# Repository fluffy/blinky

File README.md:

# blinky

Blinking lights to tell time. And it beeps.

# Build and flash

Build with:
```
mkdir build ; cd build ; cmake .. ; make
```

Note when programming the GPS board, the GPS must be unplugged while
programming.

Program flash using stlink with:
```
st-flash --reset --format ihex write build/blinky.hex
```

Can program using Stm32CubeProgrammer with RTS=1, DTR=0, baud at 115200,
Parity Even, data bits 8, stop bits 1, flow control off.

Program flash using USB serial with:
```
stm32flash -w build/blinky.hex -v -b 115200 -m 8e1 -i "-dtr," /dev/cu.usbserial-31110
```

If this fails, try the following reset then try to flash again. This
will not work on a brand new uninitialized board, the board needs to be
programmed for the first time with st-flash.

Can reset the board with:
```
stty -f /dev/cu.usbserial-31110 hup
```

Monitor output connect with Serial program. Use 115200 baud with 8 bits,
no parity, 1 stop bit. Set the RTS and DTR both low. Screen fails to do
this. It sets RTS and DTR both high it will not work.

To use python miniterm (replace usbserial-31110 with number on your machine):
```
pyserial-miniterm -e --parity N --rts 0 --dtr 0 /dev/cu.usbserial-31110 115200
```
Can exit the miniterm with CTRL+]. This will cause board reset when it starts.

# Tools and Dependencies

Set up a mac to be able to build by installing:

* TODO
* pip3 install pyserial

# Features

## Blink Timing Board

On the Rev A hardware 1.0 software have:

* Timing board with TXCO, LTC Sync in, LTC Sync out, LED grid,
  battery power, USB debug, audio in/out

* Display 120 fps tick on 10x4 grid
* 3.3V LTC Sync Out
* PPS out is hold sync button while booting
* Jitter of less than 1 ms
* Jam sync to 3.3V Sync input
* Time drift of < 5 ms in 1 hour
* USB port for serial data
* read  calibration from EEPROM
* audio out of beep
* headset monitor of audio out
* usb upgrade of firmware
* Status LEDs: error(red), external synced (green),  not sync (
  blue ), have sync (teal)
* audio input to detect beep
* battery with 2h life and USB charger

## Clock and GPS Board

On the Rev A hardware 0.2 software have:

* GPS board with GPS, OCXO
* LTC sync out, LTC sync in
* Does not have audio or led display grid
* 10 MHz sine wave output 1V p2p into 50 ohm, 3 channels
* Sync to GPS PPS
* Show current PPS offset from GPS PPS
* Compare PPS accuracy to GPS over 24 hours
* read  calibration from EEPROM
* USB serial display of: Time, GPS Error, SyncIn Error
* Aux input of 10 MHz signal to compare
* PPS jitter of about +/- 20 ns and error less than 10 ns
* USB upgrade of firmware
* USB 3A power for gps board
* USB output serial data for computer time sync

## Light GPS Board

On the Rev A hardware 0.2 software have:

* GPS board with GPS
* LTC sync out
* Does not have audio or led display grid
* Sync to GPS PPS
* USB upgrade of firmware
* USB power
* USB output serial data for computer time sync

## Wishlist

* time into browser measure computer time offset
* software upgrade from browser

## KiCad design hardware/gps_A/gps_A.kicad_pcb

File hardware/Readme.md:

# Notes on updating hardware

If the schematic or boards in changed such that the software can tell
the difference, the rev need to go up a letter. Other changes can get a
sub number on the rev letter.

## Schematics

Don't update sybols  / footprint from libraries. It over writes stuff.

When done, do a plot to generate schematic in production subdir.

## PCB

When done, do an export of step to generate a model in production
subdir.

## JLCPCB

Make sure to have them check part placement becuase it will be
wrong. Even what they have in the preivewi tool does not allways match
what they have in productions.

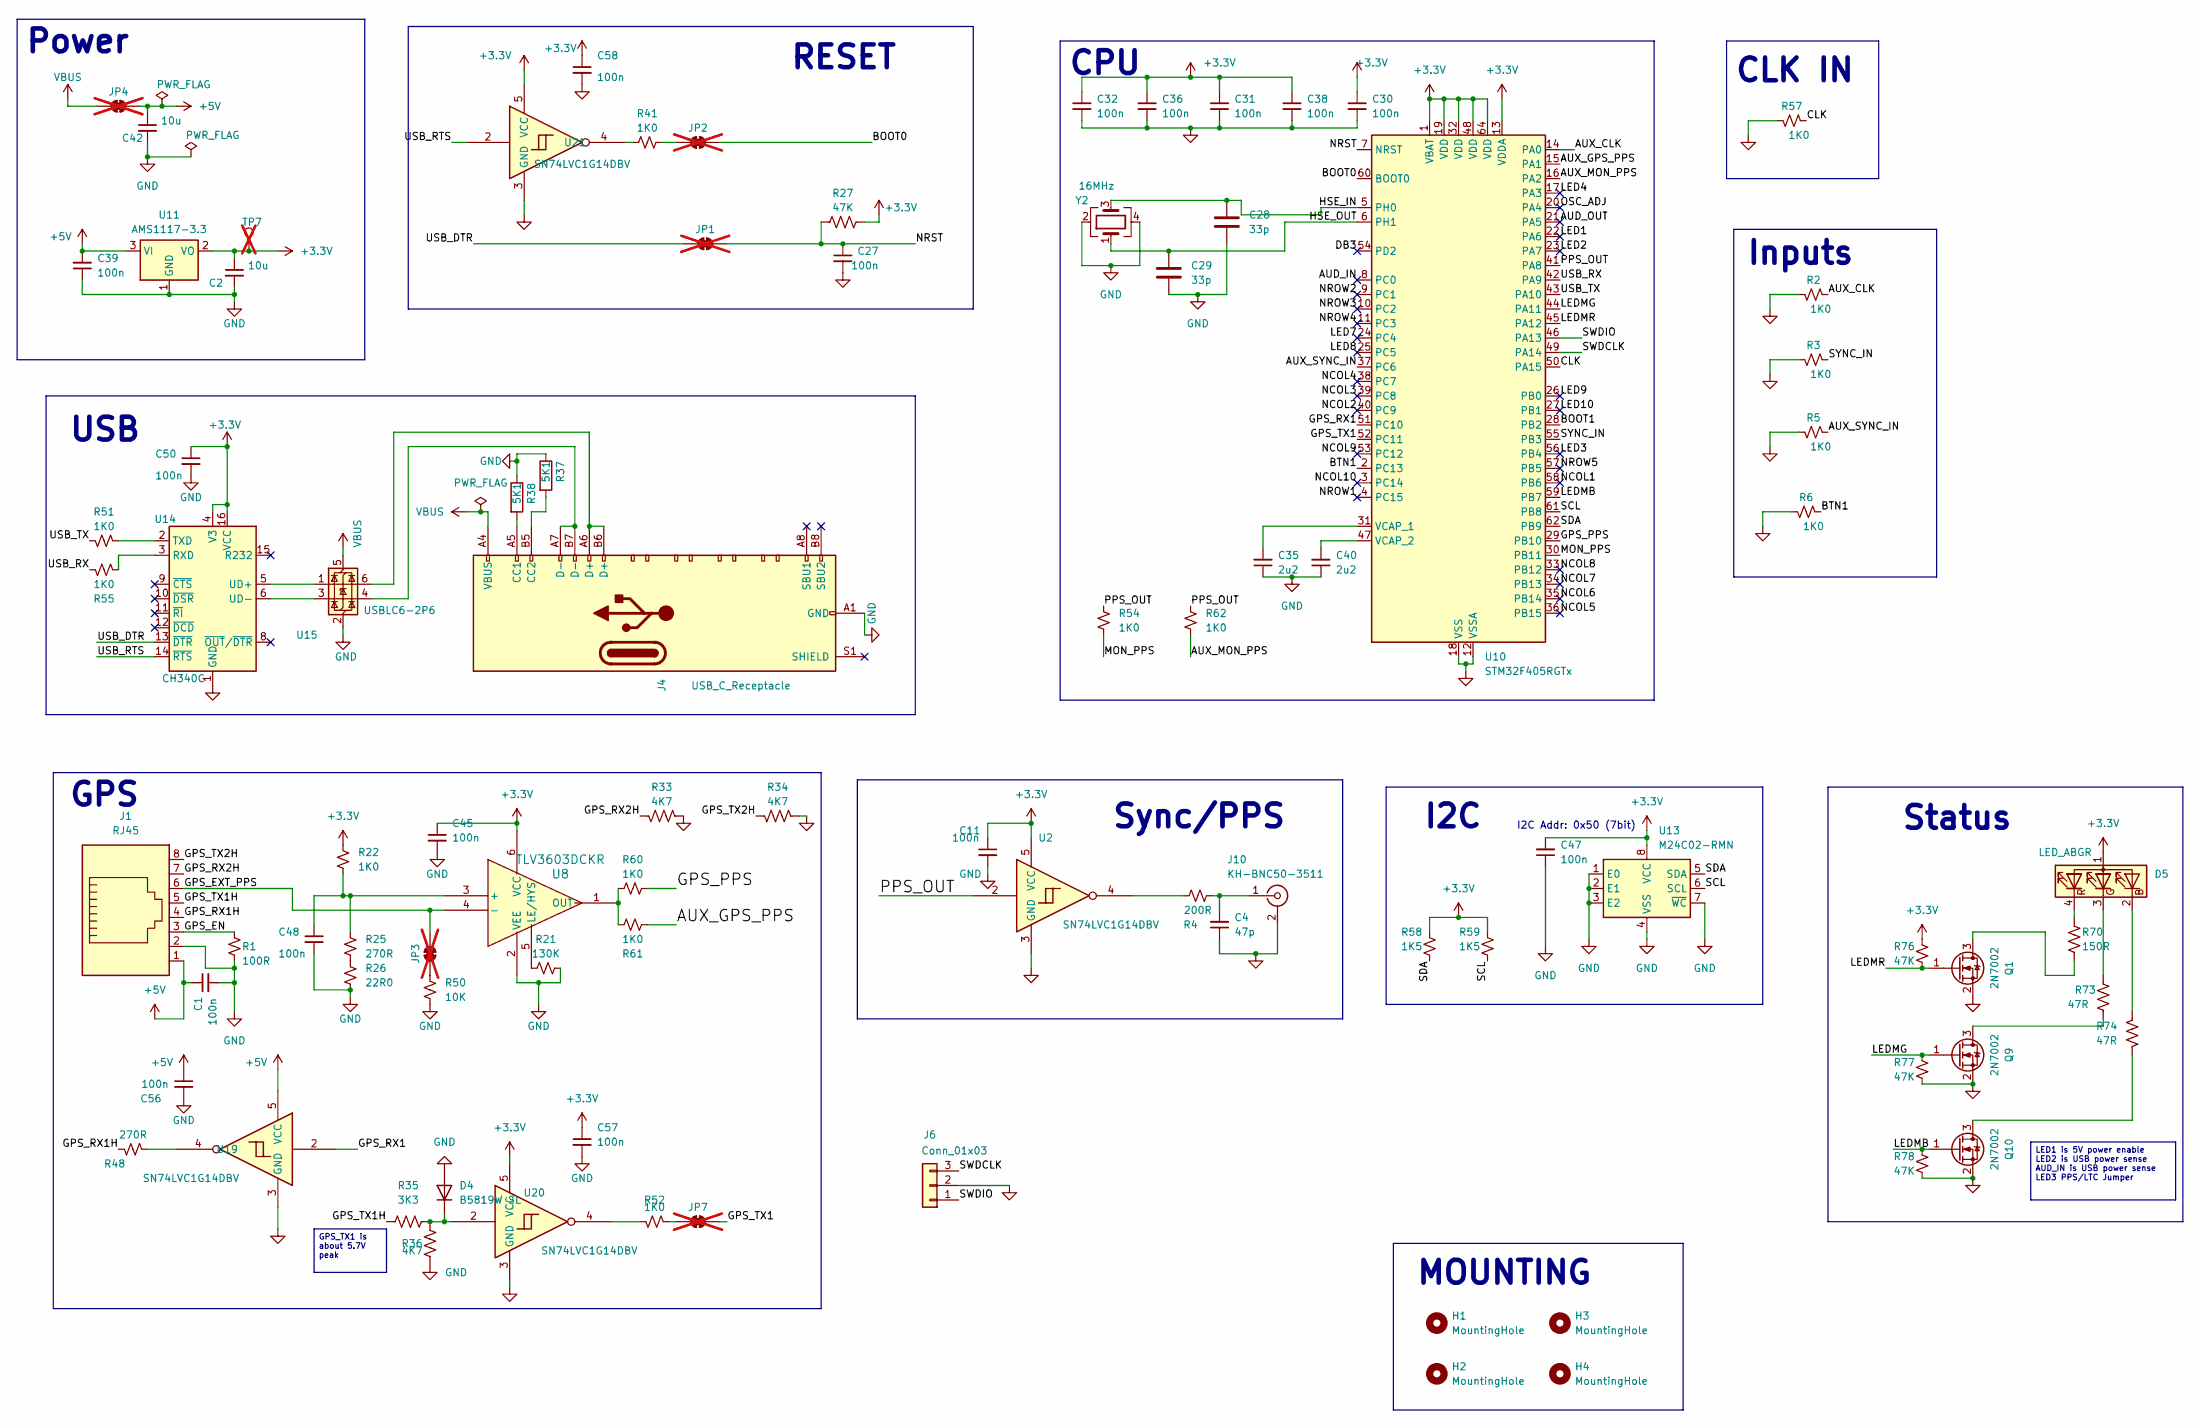
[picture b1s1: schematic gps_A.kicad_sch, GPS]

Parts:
C1, C11, C30, C31, C32, C36, C38, C39, C45, C47, C48, C50, C56, C57, C58: 100n; C_0402_1005Metric; JLCPCB Part # C307331
C2, C42: 10u; C_0603_1608Metric; JLCPCB Part # C19702
C4: 47p; C_0603_1608Metric; JLCPCB Part # C1671
C27: 100n; C_0603_1608Metric; JLCPCB Part # C14663
C28, C29: 33p; C_0603_1608Metric; JLCPCB Part # C1663
C35, C40: 2u2; C_0603_1608Metric; JLCPCB Part # C23630
D4: B5819W SL; D_SOD-123; JLCPCB Part # C8598
D5: LED_ABGR; LED_RGB_MHS110FRGBCT; MPN MHS110FRGBCT; JLCPCB Part # C496820
H1, H2, H3, H4: MountingHole; MountingHole_2.2mm_M2
J1: RJ45; RJ45_Amphenol_RJHSE5380; JLCPCB Part # C464586
J4: USB_C_Receptacle; USB_C_Receptacle_HRO_TYPE-C-31-M-12; JLCPCB Part # C165948
J6: Conn_01x03; JST_PH_S3B-PH-SM4-TB_1x03-1MP_P2.00mm_Horizontal; JLCPCB Part # C265101
J10: KH-BNC50-3511; BNC_Amphenol_B6252HB-NPP3G-50_Horizontal-CJ; JLCPCB Part # C2837587
JP1, JP2, JP3, JP4, JP7: SolderJumper_2_Bridged; SolderJumper-2_P1.3mm_Bridged2Bar_RoundedPad1.0x1.5mm; not fitted
Q1, Q9, Q10: 2N7002; SOT-23; JLCPCB Part # C8545
R1: 100R; R_0603_1608Metric; JLCPCB Part # C22775
R2, R3, R5, R6, R22, R41, R51, R52, R54, R55, R57, R60, R61, R62: 1K0; R_0603_1608Metric; JLCPCB Part # C21190
R4: 200R; R_0603_1608Metric; JLCPCB Part # C8218
R21: 130K; R_0603_1608Metric; JLCPCB Part # C22795
R25, R48: 270R; R_0603_1608Metric; JLCPCB Part # C22966
R26: 22R0; R_0603_1608Metric; JLCPCB Part # C23345
R27, R76, R77, R78: 47K; R_0603_1608Metric; JLCPCB Part # C25819
R33, R34, R36: 4K7; R_0603_1608Metric; JLCPCB Part # C23162
R35: 3K3; R_0603_1608Metric; JLCPCB Part # C22978
R37, R38: 5K1; R_0603_1608Metric; JLCPCB Part # C23186
R50: 10K; R_0603_1608Metric; JLCPCB Part # C25804
R58, R59: 1K5; R_0603_1608Metric; JLCPCB Part # C22843
R70: 150R; R_0603_1608Metric; JLCPCB Part # C22808
R73, R74: 47R; R_0603_1608Metric; JLCPCB Part # C23182
TP7: TestPoint_THTPad_D1.5mm_Drill0.7mm; not fitted
U2, U19, U20, U21: SN74LVC1G14DBV; SOT-23-5; JLCPCB Part # C133145
U8: TLV3603DCKR; SOT-363_SC-70-6; JLCPCB Part # C5213955
U10: STM32F405RGTx; LQFP-64_10x10mm_P0.5mm; JLCPCB Part # C15742
U11: AMS1117-3.3; SOT-223-3_TabPin2; JLCPCB Part # C6186
U13: M24C02-RMN; SOIC-8_3.9x4.9mm_P1.27mm; JLCPCB Part # C83836
U14: CH340C; SOIC-16_3.9x9.9mm_P1.27mm; JLCPCB Part # C7464026
U15: USBLC6-2P6; SOT-666; JLCPCB Part # C2827693
Y2: 16MHz; Crystal_SMD_3225-4Pin_3.2x2.5mm; JLCPCB Part # C13738

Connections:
+3.3V: C2.1, C11.1, C30.1, C31.1, C32.1, C36.1, C38.1, C45.1, C47.2, C50.1, C57.1, C58.1, D5.1 (A), R22.1, R27.1, R58.1, R59.1, R76.1, TP7.1, U2.5 (VCC), U8.6 (VCC), U10.1 (VBAT), U10.13 (VDDA), U10.19 (VDD), U10.32 (VDD), U10.48 (VDD), U10.64 (VDD), U11.2 (VO), U13.8 (VCC), U14.4 (V3), U14.16 (VCC), U20.5 (VCC), U21.5 (VCC)
+5V: C1.1, C39.2, C42.1, C56.1, J1.1, JP4.2 (B), U11.3 (VI), U19.5 (VCC)
/AUD_IN: U10.8 (PC0)
/AUD_OUT: U10.21 (PA5)
/AUX_CLK: R2.1, U10.14 (PA0)
/AUX_GPS_PPS: R61.2, U10.15 (PA1)
/AUX_MON_PPS: R62.2, U10.16 (PA2)
/AUX_SYNC_IN: R5.1, U10.37 (PC6)
/BOOT0: JP2.2 (B), U10.60 (BOOT0)
/BOOT1: U10.28 (PB2)
/BTN1: R6.1, U10.2 (PC13)
/CLK: R57.1, U10.50 (PA15)
/DB3: U10.54 (PD2)
/GPS_EN: J1.3, R1.1
/GPS_EXT_PPS: J1.6, JP3.2 (B), U8.4 (-)
/GPS_PPS: R60.1, U10.29 (PB10)
/GPS_RX1: U10.51 (PC10), U19.2
/GPS_RX1H: J1.4, R48.2
/GPS_RX2H: J1.7, R33.2
/GPS_TX1: JP7.2 (B), U10.52 (PC11)
/GPS_TX1H: J1.5, R35.2
/GPS_TX2H: J1.8, R34.2
/HSE_IN: C28.1, U10.5 (PH0), Y2.3
/HSE_OUT: C29.1, U10.6 (PH1), Y2.1
/LED1: U10.22 (PA6)
/LED2: U10.23 (PA7)
/LED3: U10.56 (PB4)
/LED4: U10.17 (PA3)
/LED7: U10.24 (PC4)
/LED8: U10.25 (PC5)
/LED9: U10.26 (PB0)
/LED10: U10.27 (PB1)
/LEDMB: Q10.1 (G), R78.1, U10.59 (PB7)
/LEDMG: Q9.1 (G), R77.1, U10.44 (PA11)
/LEDMR: Q1.1 (G), R76.2, U10.45 (PA12)
/MON_PPS: R54.2, U10.30 (PB11)
/NCOL1: U10.58 (PB6)
/NCOL2: U10.40 (PC9)
/NCOL3: U10.39 (PC8)
/NCOL4: U10.38 (PC7)
/NCOL5: U10.36 (PB15)
/NCOL6: U10.35 (PB14)
/NCOL7: U10.34 (PB13)
/NCOL8: U10.33 (PB12)
/NCOL9: U10.53 (PC12)
/NCOL10: U10.3 (PC14)
/NROW1: U10.4 (PC15)
/NROW2: U10.9 (PC1)
/NROW3: U10.10 (PC2)
/NROW4: U10.11 (PC3)
/NROW5: U10.57 (PB5)
/NRST: C27.1, JP1.2 (B), R27.2, U10.7 (NRST)
/OSC_ADJ: U10.20 (PA4)
/PPS_OUT: R54.1, R62.1, U2.2, U10.41 (PA8)
/SCL: R59.2, U10.61 (PB8), U13.6 (SCL)
/SDA: R58.2, U10.62 (PB9), U13.5 (SDA)
/SWDCLK: J6.3, U10.49 (PA14)
/SWDIO: J6.1, U10.46 (PA13)
/SYNC_IN: R3.1, U10.55 (PB3)
/USB_DTR: JP1.1 (A), U14.13 (~DTR)
/USB_RTS: U14.14 (~RTS), U21.2
/USB_RX: R55.1, U10.42 (PA9)
/USB_TX: R51.2, U10.43 (PA10)
GND: C1.2, C2.2, C4.1, C11.2, C27.2, C28.2, C29.2, C30.2, C31.2, C32.2, C35.1, C36.2, C38.2, C39.1, C40.1, C42.2, C45.2, C47.1, C48.2, C50.2, C56.2, C57.2, C58.2, D4.2 (A), J1.2, J4.A1 (GND), J4.A12 (GND), J4.B1 (GND), J4.B12 (GND), J6.2, J10.2 (Ext), Q1.2 (S), Q9.2 (S), Q10.2 (S), R1.2, R2.2, R3.2, R5.2, R6.2, R21.2, R26.2, R33.1, R34.1, R36.1, R37.1, R38.1, R50.2, R57.2, R77.2, R78.2, U2.3 (GND), U8.2 (VEE), U10.12 (VSSA), U10.18 (VSS), U10.63 (VSS), U11.1 (GND), U13.1 (E0), U13.2 (E1), U13.3 (E2), U13.4 (VSS), U13.7 (~WC), U14.1 (GND), U15.2 (GND), U19.3 (GND), U20.3 (GND), U21.3 (GND), Y2.2, Y2.4
unnamed: D4.1 (K), R35.1, R36.2, U20.2
unnamed: D5.2 (BK), R74.1
unnamed: D5.3 (GK), R73.2
unnamed: D5.4 (RK), R70.2
unnamed: J4.A5 (CC1), R38.2
unnamed: J4.B5 (CC2), R37.2
unnamed: J4.A6 (D+), J4.B6 (D+), U15.6 (I/O1)
unnamed: J4.A7 (D-), J4.B7 (D-), U15.4 (I/O2)
unnamed: C4.2, J10.1 (In), R4.2
unnamed: JP2.1 (A), R41.2
unnamed: JP3.1 (A), R50.1
unnamed: JP7.1 (A), R52.1
unnamed: Q1.3 (D), R70.1
unnamed: Q9.3 (D), R73.1
unnamed: Q10.3 (D), R74.2
unnamed: R4.1, U2.4
unnamed: R25.2, R26.1
unnamed: R41.1, U21.4
unnamed: R48.1, U19.4
unnamed: R52.2, U20.4
unnamed: C48.1, R22.2, R25.1, U8.3 (+)
unnamed: R21.1, U8.5 (LE/HYS)
unnamed: R60.2, R61.1, U8.1 (OUT)
unnamed: C35.2, U10.31 (VCAP_1)
unnamed: C40.2, U10.47 (VCAP_2)
unnamed: R55.2, U14.3 (RXD)
unnamed: R51.1, U14.2 (TXD)
unnamed: U14.5 (UD+), U15.1 (I/O1)
unnamed: U14.6 (UD-), U15.3 (I/O2)
VBUS: J4.A4 (VBUS), J4.A9 (VBUS), J4.B4 (VBUS), J4.B9 (VBUS), JP4.1 (A), U15.5 (VBUS)

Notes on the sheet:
RESET
USB
GPS
Inputs
CPU
I2C
Status
Sync/PPS
CLK IN
MOUNTING
I2C Addr: 0x50 (7bit)
Power
LED1 is 5V power enable LED2 is USB power sense AUD_IN is USB power sense LED3 PPS/LTC Jumper
GPS_TX1 is about 5.7V peak

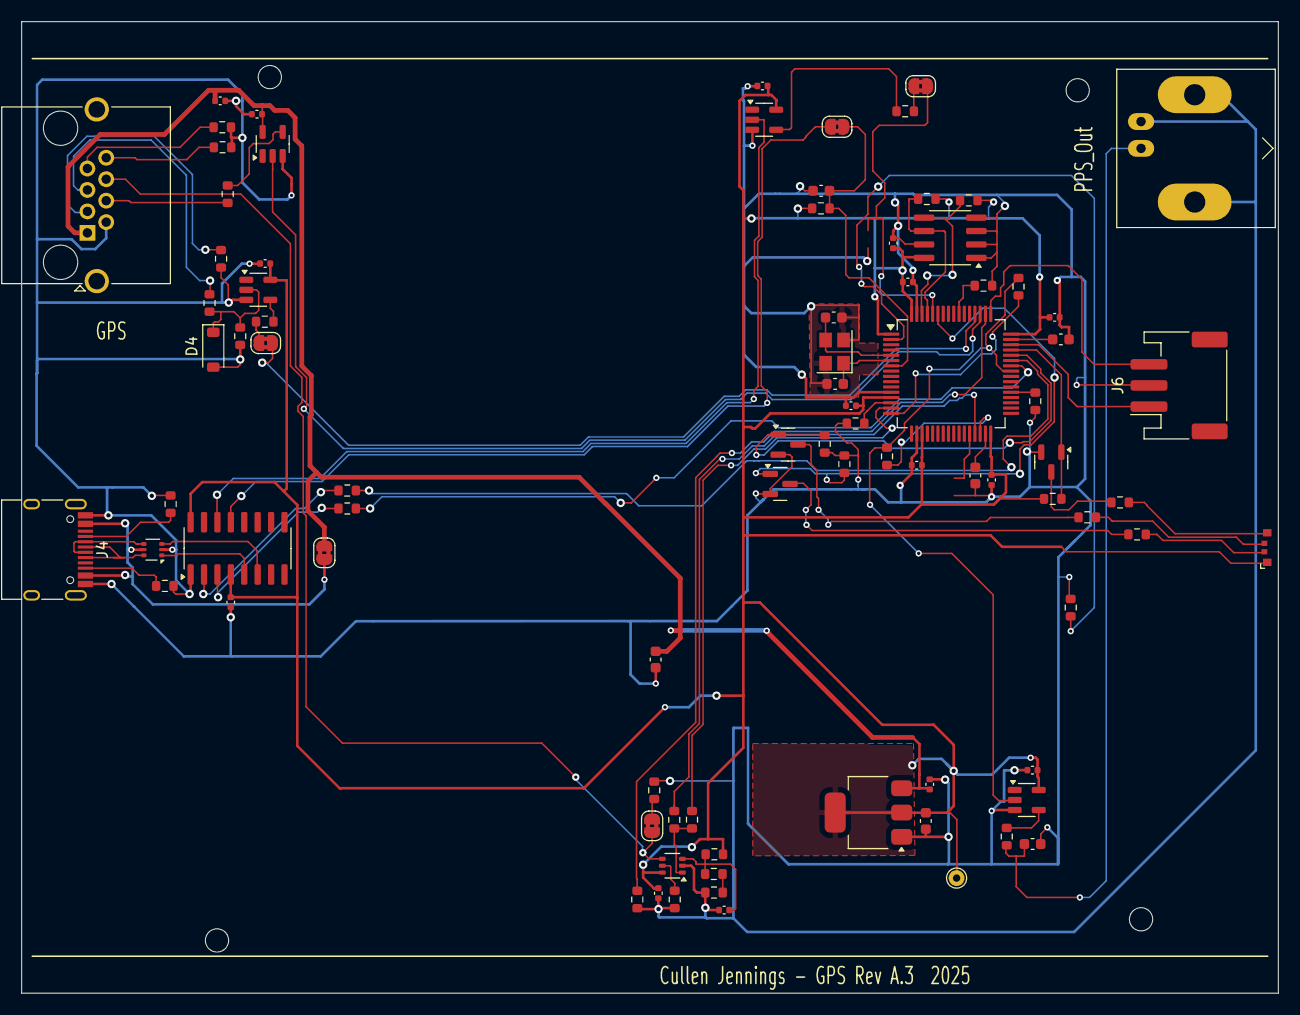
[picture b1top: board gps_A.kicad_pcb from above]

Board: 2 copper layers, 119.0 x 92.0 mm, 89 parts (0 on the bottom side), 66 nets.

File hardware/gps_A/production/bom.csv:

Designator,Footprint,Quantity,Value,LCSC Part #
"C1, C11, C30, C31, C32, C36, C38, C39, C45, C47, C48, C50, C56, C57, C58",0402,15,100n,C307331
"C2, C42",0603,2,10u,C19702
C27,0603,1,100n,C14663
"C28, C29",0603,2,33p,C1663
"C35, C40",0603,2,2u2,C23630
C4,0603,1,47p,C1671
D4,D_SOD-123,1,B5819W SL,C8598
D5,LED_RGB_MHS110FRGBCT,1,LED_ABGR,C496820
J1,RJ45_Amphenol_RJHSE5380,1,RJ45,C464586
J10,BNC_Amphenol_B6252HB-NPP3G-50_Horizontal-CJ,1,KH-BNC50-3511,C2837587
J4,USB_C_Receptacle_HRO_TYPE-C-31-M-12,1,USB_C_Receptacle,C165948
"Q1, Q10, Q9",SOT-23,3,2N7002,C8545
R1,0603,1,100R,C22775
"R2, R22, R3, R41, R5, R51, R52, R54, R55, R57, R6, R60, R61, R62",0603,14,1K0,C21190
R21,0603,1,130K,C22795
"R25, R48",0603,2,270R,C22966
R26,0603,1,22R0,C23345
"R27, R28, R76, R77, R78",0603,5,47K,C25819
"R32, R33, R34, R36",0603,4,4K7,C23162
R35,0603,1,3K3,C22978
"R37, R38",0603,2,5K1,C23186
R4,0603,1,200R,C8218
R50,0603,1,10K,C25804
"R58, R59",0603,2,1K5,C22843
R70,0603,1,150R,C22808
"R73, R74",0603,2,47R,C23182
U10,LQFP-64_10x10mm_P0.5mm,1,STM32F405RGTx,C15742
U11,SOT-223-3_TabPin2,1,AMS1117-3.3,C6186
U13,SOIC-8_3.9x4.9mm_P1.27mm,1,M24C02-RMN,C83836
U14,SOIC-16_3.9x9.9mm_P1.27mm,1,CH340C,C7464026
U15,SOT-666,1,USBLC6-2P6,C2827693
"U19, U2, U20, U21",SOT-23-5,4,SN74LVC1G14DBV,C133145
U8,SOT-363_SC-70-6,1,TLV3603DCKR,C5213955
Y2,Crystal_SMD_3225-4Pin_3.2x2.5mm,1,16MHz ,C13738

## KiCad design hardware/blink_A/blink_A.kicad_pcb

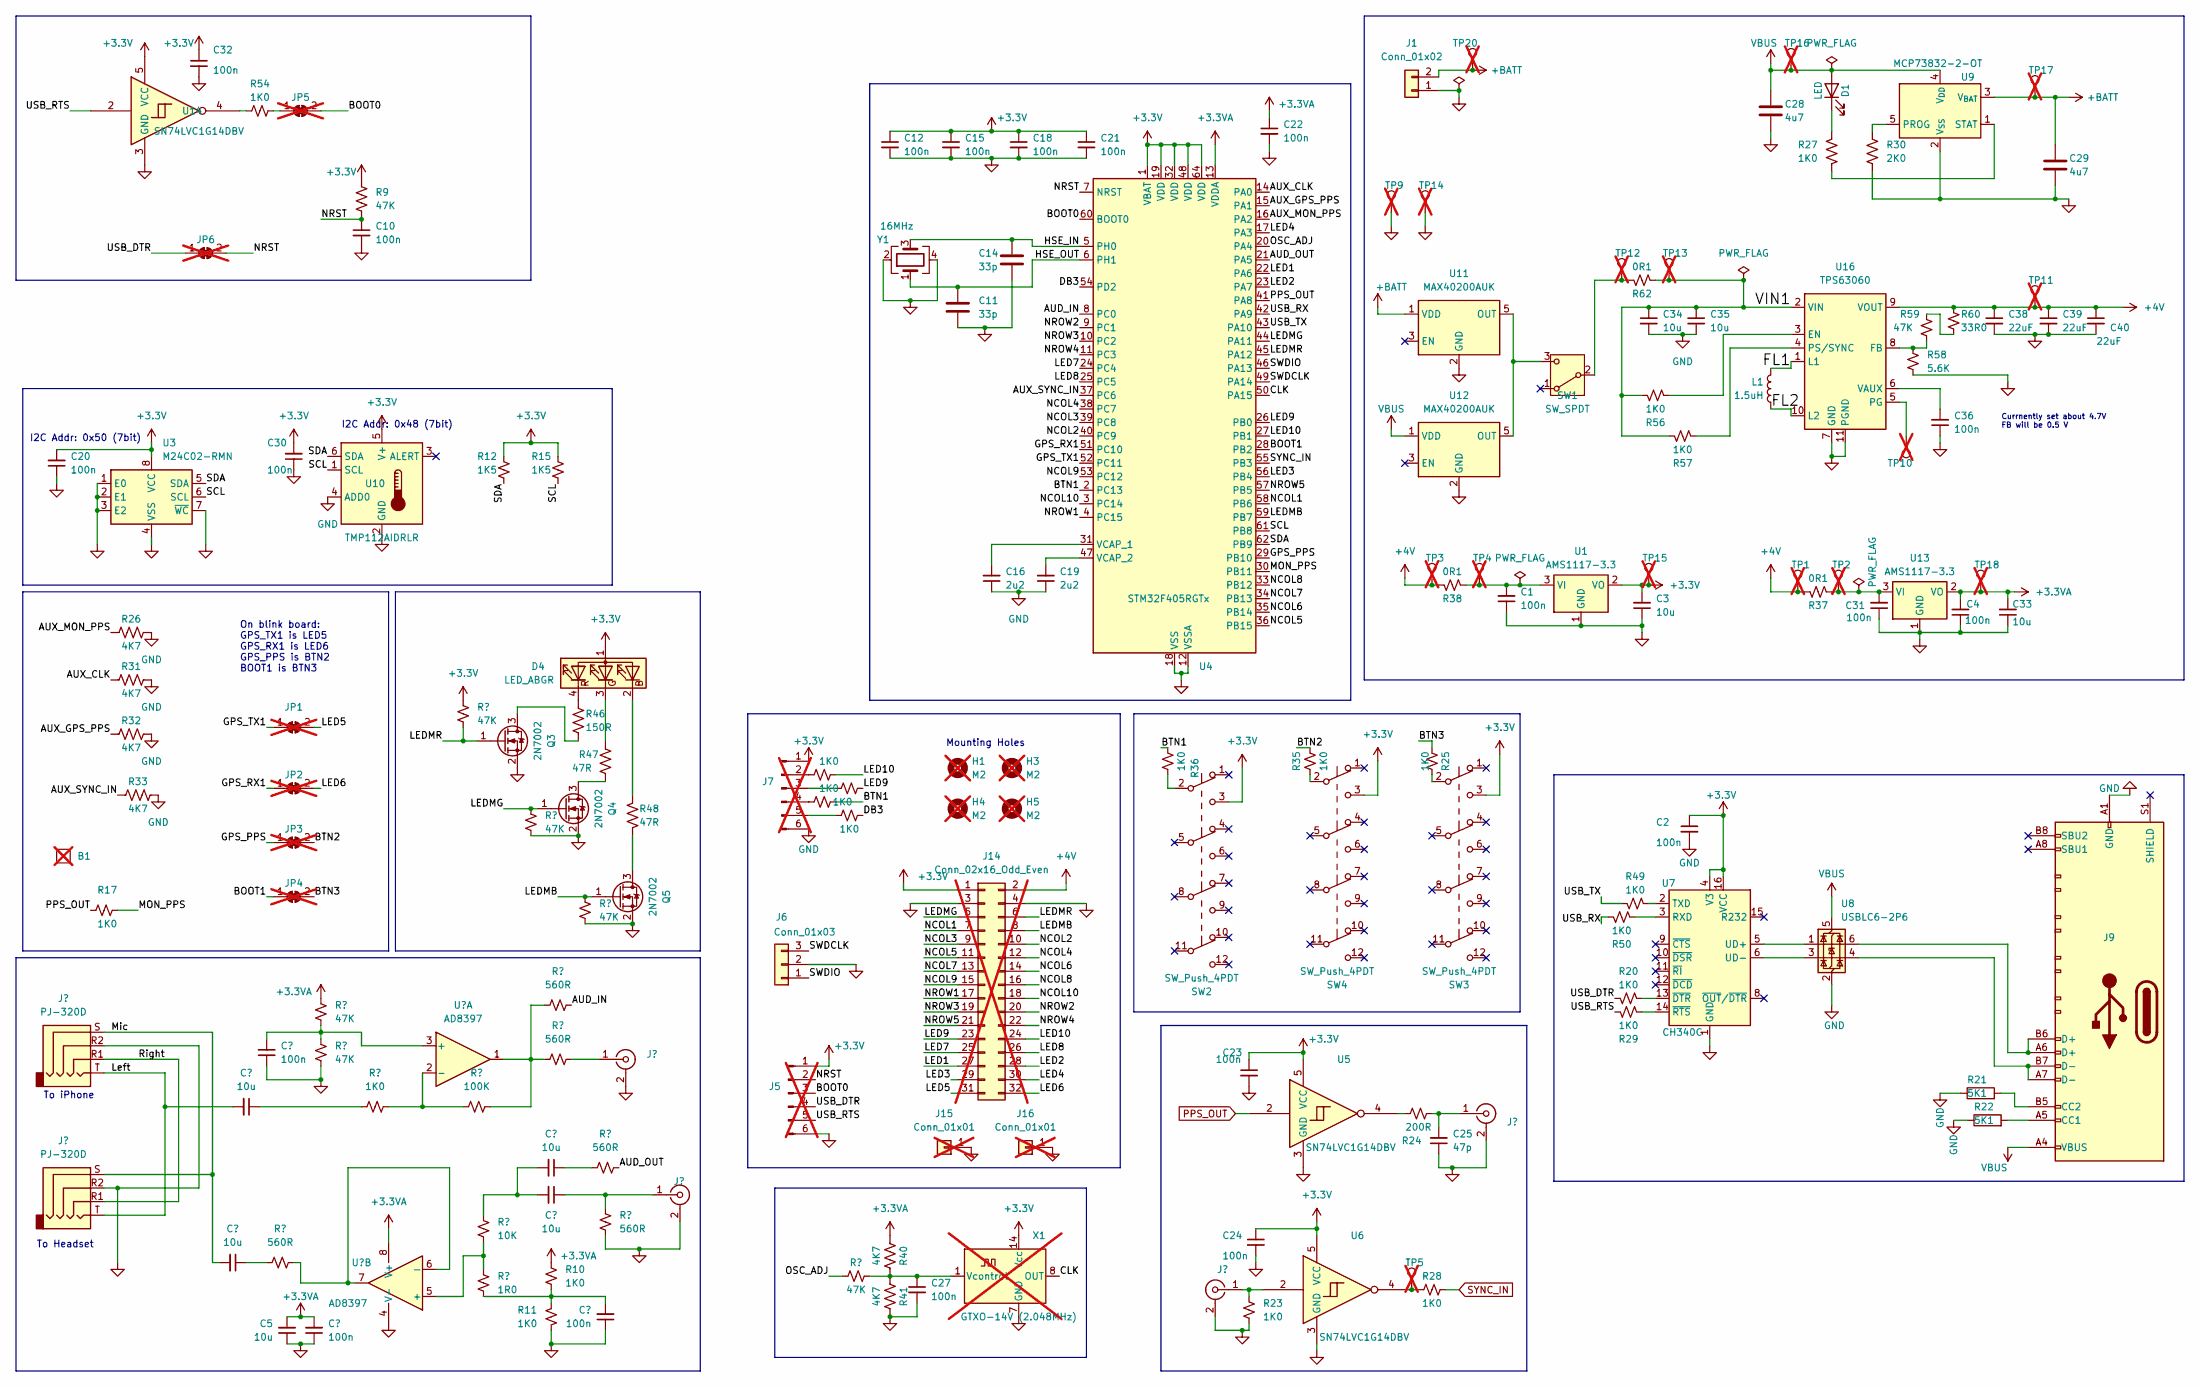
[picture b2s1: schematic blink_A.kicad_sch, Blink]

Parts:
B1: BatteryFlat1; not fitted
C1, C2, C12, C15, C18, C20, C21, C22, C23, C24, C30, C31, C32: 100n; C_0402_1005Metric; JLCPCB Part # C307331
C3, C5, C7, C8, C13, C26, C33: 10u; C_0603_1608Metric; JLCPCB Part # C19702
C4, C6, C9, C10, C17, C27, C36: 100n; C_0603_1608Metric; JLCPCB Part # C14663
C11, C14: 33p; C_0603_1608Metric; JLCPCB Part # C1663
C16, C19: 2u2; C_0603_1608Metric; JLCPCB Part # C23630
C25: 47p; C_0603_1608Metric; JLCPCB Part # C1671
C28, C29: 4u7; C_0603_1608Metric; JLCPCB Part # C19666
C34, C35: 10u; C_0603_1608Metric; JLCPCB Part # C96446
C38, C39, C40: 22uF; C_0805_2012Metric; JLCPCB Part # C45783
D1: LED; LED_0805_2012Metric; JLCPCB Part # C130114
D4: LED_ABGR; LED_RGB_MHS110FRGBCT; MPN MHS110FRGBCT; JLCPCB Part # C496820
H1, H3, H4, H5: M2; MountingHole_2.2mm_M2; not fitted
J1: Conn_01x02; JST_PH_S2B-PH-SM4-TB_1x02-1MP_P2.00mm_Horizontal; JLCPCB Part # C295747
J2, J3: PJ-320D; Jack_3.5mm_PJ320D_Horizontal-CJ; MPN PJ-320D; JLCPCB Part # C431535
J4, J11, J12, J13: KH-BNC50-3511; BNC_Amphenol_B6252HB-NPP3G-50_Horizontal-CJ; MPN KH-BNC50-3511; JLCPCB Part # C2837587
J5, J7: Conn_01x06_Pin; PinHeader_1x06_P2.54mm_Vertical; not fitted
J6: Conn_01x03; JST_PH_S3B-PH-SM4-TB_1x03-1MP_P2.00mm_Horizontal; JLCPCB Part # C265101
J9: USB_C_Receptacle; USB_C_Receptacle_HRO_TYPE-C-31-M-12; JLCPCB Part # C165948
J14: Conn_02x16_Odd_Even; PinHeader_2x16_P2.54mm_Vertical; not fitted
J15, J16: Conn_01x01; PinSocket_1x01_P2.54mm_Vertical; not fitted
JP1, JP2, JP3, JP4: SolderJumper_2_Bridged; SolderJumper-2_P1.3mm_Bridged_RoundedPad1.0x1.5mm; not fitted
JP5, JP6: SolderJumper_2_Bridged; SolderJumper-2_P1.3mm_Bridged2Bar_RoundedPad1.0x1.5mm; not fitted
L1: 1.5uH; L_Coilcraft_XAL4020-XXX; MPN XFL4020-152MEC; JLCPCB Part # C3033018
Q3, Q4, Q5: 2N7002; SOT-23; JLCPCB Part # C8545
R1, R2, R13, R16, R19: 560R; R_0603_1608Metric; JLCPCB Part # C23204
R3, R4, R9, R39, R51, R52, R53, R59: 47K; R_0603_1608Metric; JLCPCB Part # C25819
R5, R10, R11, R17, R20, R23, R25, R27, R28, R29, R35, R36, R42, R43, R44, R45, R49, R50, R54, R56, R57: 1K0; R_0603_1608Metric; JLCPCB Part # C21190
R6: 10K; R_0603_1608Metric; JLCPCB Part # C25804
R7: 1R0; R_0603_1608Metric; JLCPCB Part # C22936
R8: 100K; R_0603_1608Metric; JLCPCB Part # C25803
R12, R15: 1K5; R_0603_1608Metric; JLCPCB Part # C22843
R21, R22: 5K1; R_0603_1608Metric; JLCPCB Part # C23186
R24: 200R; R_0603_1608Metric; JLCPCB Part # C8218
R26, R31, R32, R33, R40, R41: 4K7; R_0603_1608Metric; JLCPCB Part # C23162
R30: 2K0; R_0603_1608Metric; JLCPCB Part # C22975
R37, R38, R62: 0R1; R_1206_3216Metric; JLCPCB Part # C25334
R46: 150R; R_0603_1608Metric; JLCPCB Part # C22808
R47, R48: 47R; R_0603_1608Metric; JLCPCB Part # C23182
R58: 5.6K; R_0603_1608Metric; JLCPCB Part # C23189
R60: 33R0; R_0603_1608Metric; JLCPCB Part # C23140
SW1: SW_SPDT; SW_E-Switch_EG1224_SPDT_Angled; JLCPCB Part # C273395
SW2, SW3, SW4: SW_Push_4PDT; PBH4UOANAGX; JLCPCB Part # C273424
TP1, TP2, TP3, TP4, TP12, TP13: TestPoint_THTPad_D1.0mm_Drill0.5mm; not fitted
TP5, TP9, TP10, TP11, TP14, TP15, TP16, TP17, TP18, TP20: TestPoint_THTPad_D1.5mm_Drill0.7mm; not fitted
U1, U13: AMS1117-3.3; SOT-223-3_TabPin2; JLCPCB Part # C6186
U2: AD8397; SOIC-8_3.9x4.9mm_P1.27mm; JLCPCB Part # C578714
U3: M24C02-RMN; SOIC-8_3.9x4.9mm_P1.27mm; JLCPCB Part # C83836
U4: STM32F405RGTx; LQFP-64_10x10mm_P0.5mm; JLCPCB Part # C15742
U5, U6, U14: SN74LVC1G14DBV; SOT-23-5; JLCPCB Part # C133145
U7: CH340C; SOIC-16_3.9x9.9mm_P1.27mm; JLCPCB Part # C7464026
U8: USBLC6-2P6; SOT-666; JLCPCB Rotation Offset 270
U9: MCP73832-2-OT; SOT-23-5; JLCPCB Part # C424093
U10: TMP112AIDRLR; SOT-563; JLCPCB Part # C28927
U11, U12: MAX40200AUK; SOT-23-5; JLCPCB Part # C2649430
U16: TPS63060; Texas_S-PWSON-N10_ThermalVias; JLCPCB Part # C48567
X1: GTXO-14V (2.048MHz); OSC_DIP-14; MPN ACVTX1018A-2.048MHZ-D10; not fitted
Y1: 16MHz; Crystal_SMD_3225-4Pin_3.2x2.5mm; JLCPCB Part # C13738

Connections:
+3.3V: C2.1, C3.2, C12.1, C15.1, C18.1, C20.2, C21.1, C23.1, C24.1, C30.2, C32.1, D4.1 (A), J5.1, J7.1, J14.1, R9.1, R12.1, R15.1, R51.2, SW2.3 (C), SW3.3 (C), SW4.3 (C), TP15.1, U1.2 (VO), U3.8 (VCC), U4.1 (VBAT), U4.19 (VDD), U4.32 (VDD), U4.48 (VDD), U4.64 (VDD), U5.5 (VCC), U6.5 (VCC), U7.4 (V3), U7.16 (VCC), U10.5 (V+), U14.5 (VCC), X1.14 (Vcc)
+3.3VA: C4.2, C5.2, C6.2, C22.1, C33.2, R3.2, R10.1, R40.1, TP18.1, U2.8 (V+), U4.13 (VDDA), U13.2 (VO)
+4V: C38.1, C39.1, C40.1, J14.2, R37.2, R38.2, R60.1, TP1.1, TP3.1, TP11.1, U16.9 (VOUT)
+BATT: C29.1, J1.2, TP17.1, TP20.1, U9.3 (V_{BAT}), U11.1 (VDD)
/AUD_IN: R1.1, U4.8 (PC0)
/AUD_OUT: R19.2, U4.21 (PA5)
/AUX_CLK: R31.1, U4.14 (PA0)
/AUX_GPS_PPS: R32.1, U4.15 (PA1)
/AUX_MON_PPS: R26.1, U4.16 (PA2)
/AUX_SYNC_IN: R33.1, U4.37 (PC6)
/BOOT0: J5.3, JP5.2 (B), U4.60 (BOOT0)
/BOOT1: JP4.1 (A), U4.28 (PB2)
/BTN1: R36.2, R44.1, U4.2 (PC13)
/BTN2: JP3.2 (B), R35.2
/BTN3: JP4.2 (B), R25.2
/CLK: U4.50 (PA15), X1.8 (OUT)
/DB3: R45.1, U4.54 (PD2)
/FL1: L1.1, U16.1 (L1)
/FL2: L1.2, U16.10 (L2)
/GPS_PPS: JP3.1 (A), U4.29 (PB10)
/GPS_RX1: JP2.1 (A), U4.51 (PC10)
/GPS_TX1: JP1.1 (A), U4.52 (PC11)
/HSE_IN: C14.1, U4.5 (PH0), Y1.3
/HSE_OUT: C11.1, U4.6 (PH1), Y1.1
/LED1: J14.27, U4.22 (PA6)
/LED2: J14.28, U4.23 (PA7)
/LED3: J14.29, U4.56 (PB4)
/LED4: J14.30, U4.17 (PA3)
/LED5: J14.31, JP1.2 (B)
/LED6: J14.32, JP2.2 (B)
/LED7: J14.25, U4.24 (PC4)
/LED8: J14.26, U4.25 (PC5)
/LED9: J14.23, R43.1, U4.26 (PB0)
/LED10: J14.24, R42.1, U4.27 (PB1)
/LEDMB: J14.8, Q5.1 (G), R53.2, U4.59 (PB7)
/LEDMG: J14.5, Q4.1 (G), R52.2, U4.44 (PA11)
/LEDMR: J14.6, Q3.1 (G), R51.1, U4.45 (PA12)
/Left: C8.2, J2.T, J3.T
/MON_PPS: R17.2, U4.30 (PB11)
/Mic: C7.2, J2.S, J3.S
/NCOL1: J14.7, U4.58 (PB6)
/NCOL2: J14.10, U4.40 (PC9)
/NCOL3: J14.9, U4.39 (PC8)
/NCOL4: J14.12, U4.38 (PC7)
/NCOL5: J14.11, U4.36 (PB15)
/NCOL6: J14.14, U4.35 (PB14)
/NCOL7: J14.13, U4.34 (PB13)
/NCOL8: J14.16, U4.33 (PB12)
/NCOL9: J14.15, U4.53 (PC12)
/NCOL10: J14.18, U4.3 (PC14)
/NROW1: J14.17, U4.4 (PC15)
/NROW2: J14.20, U4.9 (PC1)
/NROW3: J14.19, U4.10 (PC2)
/NROW4: J14.22, U4.11 (PC3)
/NROW5: J14.21, U4.57 (PB5)
/NRST: C10.1, J5.2, JP6.2 (B), R9.2, U4.7 (NRST)
/OSC_ADJ: R39.2, U4.20 (PA4)
/Right: J2.R1, J3.R1
/SCL: R15.2, U3.6 (SCL), U4.61 (PB8), U10.1 (SCL)
/SDA: R12.2, U3.5 (SDA), U4.62 (PB9), U10.6 (SDA)
/SWDCLK: J6.3, U4.49 (PA14)
/SWDIO: J6.1, U4.46 (PA13)
/USB_DTR: J5.4, JP6.1 (A), R20.2
/USB_RTS: J5.5, R29.1, U14.2
/USB_RX: R50.1, U4.42 (PA9)
/USB_TX: R49.2, U4.43 (PA10)
/VIN1: C34.1, C35.1, R56.1, R57.1, R62.1, TP13.1, U16.2 (VIN)
GND: C1.1, C2.2, C3.1, C4.1, C5.1, C6.1, C9.1, C10.2, C11.2, C12.2, C14.2, C15.2, C16.1, C17.1, C18.2, C19.1, C20.1, C21.2, C22.2, C23.2, C24.2, C25.1, C27.2, C28.2, C29.2, C30.1, C31.1, C32.2, C33.1, C34.2, C35.2, C36.1, C38.2, C39.2, C40.2, J1.1, J2.R2, J3.R2, J4.2 (Ext), J5.6, J6.2, J7.6, J9.A1 (GND), J9.A12 (GND), J9.B1 (GND), J9.B12 (GND), J11.2 (Ext), J12.2 (Ext), J13.2 (Ext), J14.3, J14.4, J15.1, J16.1, Q3.2 (S), Q4.2 (S), Q5.2 (S), R4.1, R11.2, R13.2, R21.1, R22.1, R23.2, R26.2, R30.2, R31.2, R32.2, R33.2, R41.2, R52.1, R53.1, R58.2, TP9.1, TP14.1, U1.1 (GND), U2.4 (V-), U3.1 (E0), U3.2 (E1), U3.3 (E2), U3.4 (VSS), U3.7 (~WC), U4.12 (VSSA), U4.18 (VSS), U4.63 (VSS), U5.3 (GND), U6.3 (GND), U7.1 (GND), U8.2 (GND), U9.2 (V_{SS}), U10.2 (GND), U10.4 (ADD0), U11.2 (GND), U12.2 (GND), U13.1 (GND), U14.3 (GND), U16.7 (GND), U16.11 (PGND), X1.7 (GND), Y1.2, Y1.4
unnamed: C7.1, R2.1
unnamed: C8.1, R5.2
unnamed: C13.2, C26.2, R6.1
unnamed: C17.2, R7.2, R10.2, R11.1
unnamed: C26.1, R19.1
unnamed: D1.1 (K), R27.1
unnamed: D4.2 (BK), R48.1
unnamed: D4.3 (GK), R47.2
unnamed: D4.4 (RK), R46.2
unnamed: C25.2, J4.1 (In), R24.2
unnamed: J7.2, R42.2
unnamed: J7.3, R43.2
unnamed: J7.4, R44.2
unnamed: J7.5, R45.2
unnamed: J9.A5 (CC1), R22.2
unnamed: J9.B5 (CC2), R21.2
unnamed: J9.A6 (D+), J9.B6 (D+), U8.6 (I/O1)
unnamed: J9.A7 (D-), J9.B7 (D-), U8.4 (I/O2)
unnamed: C13.1, J11.1 (In), R13.1
unnamed: J12.1 (In), R23.1, U6.2
unnamed: J13.1 (In), R16.1
unnamed: JP5.1 (A), R54.2
unnamed: Q3.3 (D), R46.1
unnamed: Q4.3 (D), R47.1
unnamed: Q5.3 (D), R48.2
unnamed: R1.2, R8.1, R16.2, U2.1
unnamed: R24.1, U5.4
unnamed: R25.1, SW3.2 (B)
unnamed: R28.2, TP5.1, U6.4
unnamed: R35.1, SW4.2 (B)
unnamed: R36.1, SW2.2 (B)
unnamed: R54.1, U14.4
unnamed: R59.1, R60.2
unnamed: R62.2, SW1.2 (B), TP12.1
unnamed: SW1.3 (C), U11.5 (OUT), U12.5 (OUT)
unnamed: C1.2, R38.1, TP4.1, U1.3 (VI)
unnamed: C9.2, R3.1, R4.2, U2.3 (+)
unnamed: R5.1, R8.2, U2.2 (-)
unnamed: R6.2, R7.1, U2.5 (+)
unnamed: R2.2, U2.6 (-), U2.7
unnamed: C16.2, U4.31 (VCAP_1)
unnamed: C19.2, U4.47 (VCAP_2)
unnamed: R50.2, U7.3 (RXD)
unnamed: R49.1, U7.2 (TXD)
unnamed: U7.5 (UD+), U8.1 (I/O1)
unnamed: U7.6 (UD-), U8.3 (I/O2)
unnamed: R20.1, U7.13 (~DTR)
unnamed: R29.2, U7.14 (~RTS)
unnamed: R30.1, U9.5 (PROG)
unnamed: R27.2, U9.1 (STAT)
unnamed: C31.2, R37.1, TP2.1, U13.3 (VI)
unnamed: R56.2, U16.3 (EN)
unnamed: R58.1, R59.2, U16.8 (FB)
unnamed: TP10.1, U16.5 (PG)
unnamed: R57.2, U16.4 (PS/SYNC)
unnamed: C36.2, U16.6 (VAUX)
unnamed: C27.1, R39.1, R40.2, R41.1, X1.1 (Vcontrol)
PPS_OUT: R17.1, U4.41 (PA8), U5.2
SYNC_IN: R28.1, U4.55 (PB3)
VBUS: C28.1, D1.2 (A), J9.A4 (VBUS), J9.A9 (VBUS), J9.B4 (VBUS), J9.B9 (VBUS), TP16.1, U8.5 (VBUS), U9.4 (V_{DD}), U12.1 (VDD)

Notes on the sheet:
I2C Addr: 0x48 (7bit)
Currnently set about 4.7V FB will be 0.5 V
To iPhone
To Headset
I2C Addr: 0x50 (7bit)
Mounting Holes
On blink board: GPS_TX1 is LED5 GPS_RX1 is LED6 GPS_PPS is BTN2 BOOT1 is BTN3

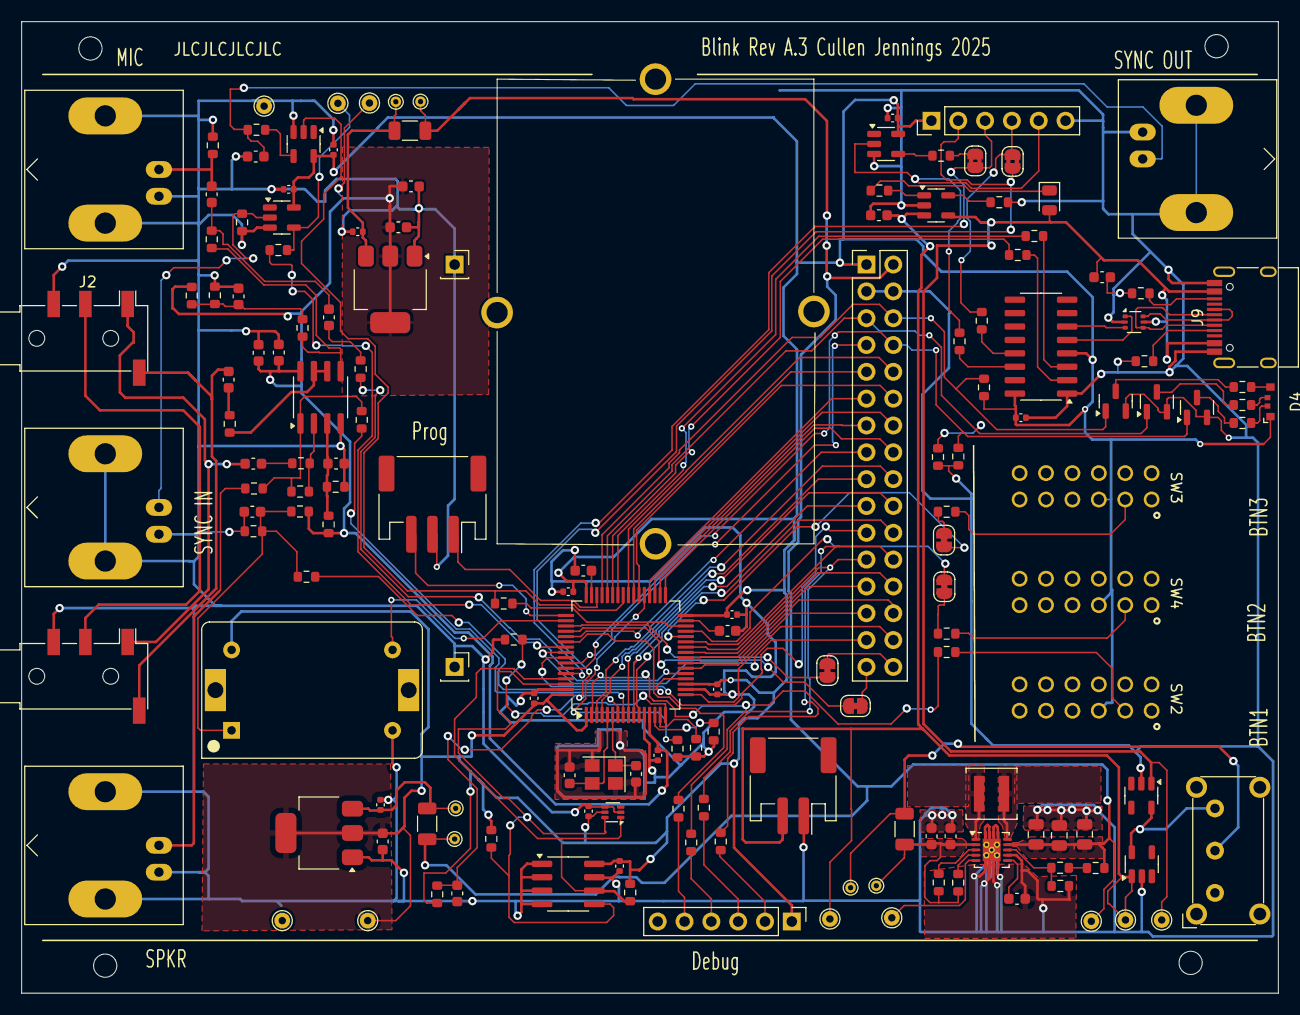
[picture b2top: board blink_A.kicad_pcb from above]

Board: 2 copper layers, 119.0 x 92.0 mm, 164 parts (0 on the bottom side), 128 nets.

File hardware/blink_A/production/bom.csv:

Designator,Footprint,Quantity,Value,LCSC Part #
"C1, C12, C15, C18, C2, C20, C21, C22, C23, C24, C30, C31, C32",0402,13,100n,C307331
"C10, C17, C27, C36, C4, C6, C9",0603,7,100n,C14663
"C11, C14",0603,2,33p,C1663
"C13, C26, C3, C33, C5, C7, C8",0603,7,10u,C19702
"C16, C19",0603,2,2u2,C23630
C25,0603,1,47p,C1671
"C28, C29",0603,2,4u7,C19666
"C34, C35",0603,2,10u,C96446
"C38, C39, C40",0805,3,22uF,C45783
D1,0805,1,LED,C130114
D4,LED_RGB_MHS110FRGBCT,1,LED_ABGR,C496820
J1,JST_PH_S2B-PH-SM4-TB_1x02-1MP_P2.00mm_Horizontal,1,Conn_01x02,C295747
"J11, J12, J13, J4",BNC_Amphenol_B6252HB-NPP3G-50_Horizontal-CJ,4,KH-BNC50-3511,C2837587
"J2, J3",Jack_3.5mm_PJ320D_Horizontal-CJ,2,PJ-320D,C431535
J6,JST_PH_S3B-PH-SM4-TB_1x03-1MP_P2.00mm_Horizontal,1,Conn_01x03,C265101
J9,USB_C_Receptacle_HRO_TYPE-C-31-M-12,1,USB_C_Receptacle,C165948
L1,L_Coilcraft_XAL4020-XXX,1,1.5uH,C3033018
"Q3, Q4, Q5",SOT-23,3,2N7002,C8545
"R1, R13, R16, R19, R2",0603,5,560R,C23204
"R10, R11, R17, R20, R23, R25, R27, R28, R29, R35, R36, R42, R43, R44, R45, R49, R5, R50, R54, R56, R57",0603,21,1K0,C21190
"R12, R15",0603,2,1K5,C22843
"R21, R22",0603,2,5K1,C23186
R24,0603,1,200R,C8218
"R26, R31, R32, R33, R40, R41",0603,6,4K7,C23162
"R3, R39, R4, R51, R52, R53, R59, R9",0603,8,47K,C25819
R30,0603,1,2K0,C22975
"R37, R38, R62",1206,3,0R1,C25334
R46,0603,1,150R,C22808
"R47, R48",0603,2,47R,C23182
R58,0603,1,5.6K,C23189
R6,0603,1,10K,C25804
R60,0603,1,33R0,C23140
R7,0603,1,1R0,C22936
R8,0603,1,100K,C25803
SW1,SW_E-Switch_EG1224_SPDT_Angled,1,SW_SPDT,C273395
"SW2, SW3, SW4",PBH4UOANAGX,3,SW_Push_4PDT,C273424
"U1, U13",SOT-223-3_TabPin2,2,AMS1117-3.3,C6186
U10,SOT-563,1,TMP112AIDRLR,C28927
"U11, U12",SOT-23-5,2,MAX40200AUK,C2649430
"U14, U5, U6",SOT-23-5,3,SN74LVC1G14DBV,C133145
U16,Texas_S-PWSON-N10_ThermalVias,1,TPS63060,C48567
U2,SOIC-8_3.9x4.9mm_P1.27mm,1,AD8397,C578714
U3,SOIC-8_3.9x4.9mm_P1.27mm,1,M24C02-RMN,C83836
U4,LQFP-64_10x10mm_P0.5mm,1,STM32F405RGTx,C15742
U7,SOIC-16_3.9x9.9mm_P1.27mm,1,CH340C,C84681
U8,SOT-666,1,USBLC6-2P6,
U9,SOT-23-5,1,MCP73832-2-OT,C424093
Y1,Crystal_SMD_3225-4Pin_3.2x2.5mm,1,16MHz ,C13738
